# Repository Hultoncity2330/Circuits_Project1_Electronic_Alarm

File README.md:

# Projet Réveil Électronique

Projet de conception d’un **réveil électronique** réalisé sous **KiCad**.  
Le dépôt contient le schéma électronique, le PCB routé, les fichiers du projet KiCad ainsi que plusieurs vues du circuit final.

## Présentation du projet

L’objectif est de concevoir un réveil électronique compact capable d’afficher l’heure sur **4 digits 7 segments**, de gérer l’heure grâce à une horloge temps réel, et de proposer une interface utilisateur simple à l’aide de boutons poussoirs.

Le circuit est organisé autour d’un **Seeed Studio XIAO ESP32-S3**, utilisé comme microcontrôleur principal.

Le PCB comprend notamment :

- un **XIAO ESP32-S3** ;
- un **RTC RV-3028-C7** pour la gestion de l’heure ;
- un **IS31FL3730** pour le pilotage des afficheurs ;
- deux afficheurs doubles **DC56-11EWA**, soit 4 digits au total ;
- un buzzer pour l’alarme ;
- un transistor MOSFET **AO3400A** pour commander le buzzer ;
- quatre boutons poussoirs : `SET`, `ALARM`, `MINUS`, `PLUS` ;
- trois LED d’indication ;
- les résistances et condensateurs nécessaires au fonctionnement du montage.

## Fonctionnement général

Le **XIAO ESP32-S3** constitue le cœur du système.

Le **RV-3028-C7** fournit l’heure au microcontrôleur via le bus **I²C** (`SDA` / `SCL`).

Le **IS31FL3730** est également relié au bus I²C et pilote les deux afficheurs 7 segments. Les deux afficheurs doubles permettent d’obtenir un affichage sur quatre chiffres.

Les boutons permettent l’interaction avec le réveil :

- `SET` : réglage ;
- `ALARM` : gestion de l’alarme ;
- `PLUS` : incrémentation ;
- `MINUS` : décrémentation.

Le buzzer est commandé par le XIAO au travers du MOSFET **AO3400A**.

## Schéma électronique

Le schéma final du projet est disponible ci-dessous :

Le fichier source KiCad correspondant est :

`Projet_Réveil_électronique.kicad_sch`

## PCB

Le PCB a été placé et routé sous KiCad sur deux couches :

- **F.Cu** : couche cuivre supérieure ;
- **B.Cu** : couche cuivre inférieure.

Le routage utilise également :

- un plan de cuivre **+3.3 V** sur la face supérieure ;
- un plan de masse **GND** sur la face inférieure.

Vue du PCB final :

Le fichier source du PCB est :

`Projet_Réveil_électronique.kicad_pcb`

## Modèle 3D

### Front view

### Back view

### Perspective view

## Validation KiCad

Le projet a été vérifié avec les outils de contrôle de KiCad.

À la fin du routage :

- **ERC** du schéma : validé ;
- **DRC** du PCB : `0` erreur ;
- **Items non connectés** : `0` ;
- **Parité schématique / PCB** : `0` erreur.

Cela permet de vérifier la cohérence électrique et le routage du projet avant la fabrication.

> La validation ERC/DRC ne remplace pas un test physique du PCB assemblé.  
> Le fonctionnement réel doit être confirmé après soudure et mise sous tension.

## Structure du dépôt

```text
.
├── Projet_Réveil_électronique.kicad_pro
├── Projet_Réveil_électronique.kicad_sch
├── Projet_Réveil_électronique.kicad_pcb
├── Schematic_Réveil_électronique_VF.png
├── PCB_VF.png
├── PCB_3D_Model_Front.png
├── PCB_3D_Model_Back.png
├── PCB_3D_Model_Perspective.png
├── .gitignore
└── README.md
```

## Fichiers principaux

| Fichier | Description |
|---|---|
| `Projet_Réveil_électronique.kicad_pro` | Fichier principal du projet KiCad |
| `Projet_Réveil_électronique.kicad_sch` | Schéma électronique |
| `Projet_Réveil_électronique.kicad_pcb` | PCB routé |
| `Schematic_Réveil_électronique_VF.png` | Image du schéma final |
| `PCB_VF.png` | Vue du PCB final |
| `PCB_3D_Model_Front.png` | Vue 3D avant |
| `PCB_3D_Model_Back.png` | Vue 3D arrière |
| `PCB_3D_Model_Perspective.png` | Vue 3D en perspective |

## Auteur

Projet réalisé dans le cadre du cours `Circuits & Embedded Devices` du `21-23/09/2026`.

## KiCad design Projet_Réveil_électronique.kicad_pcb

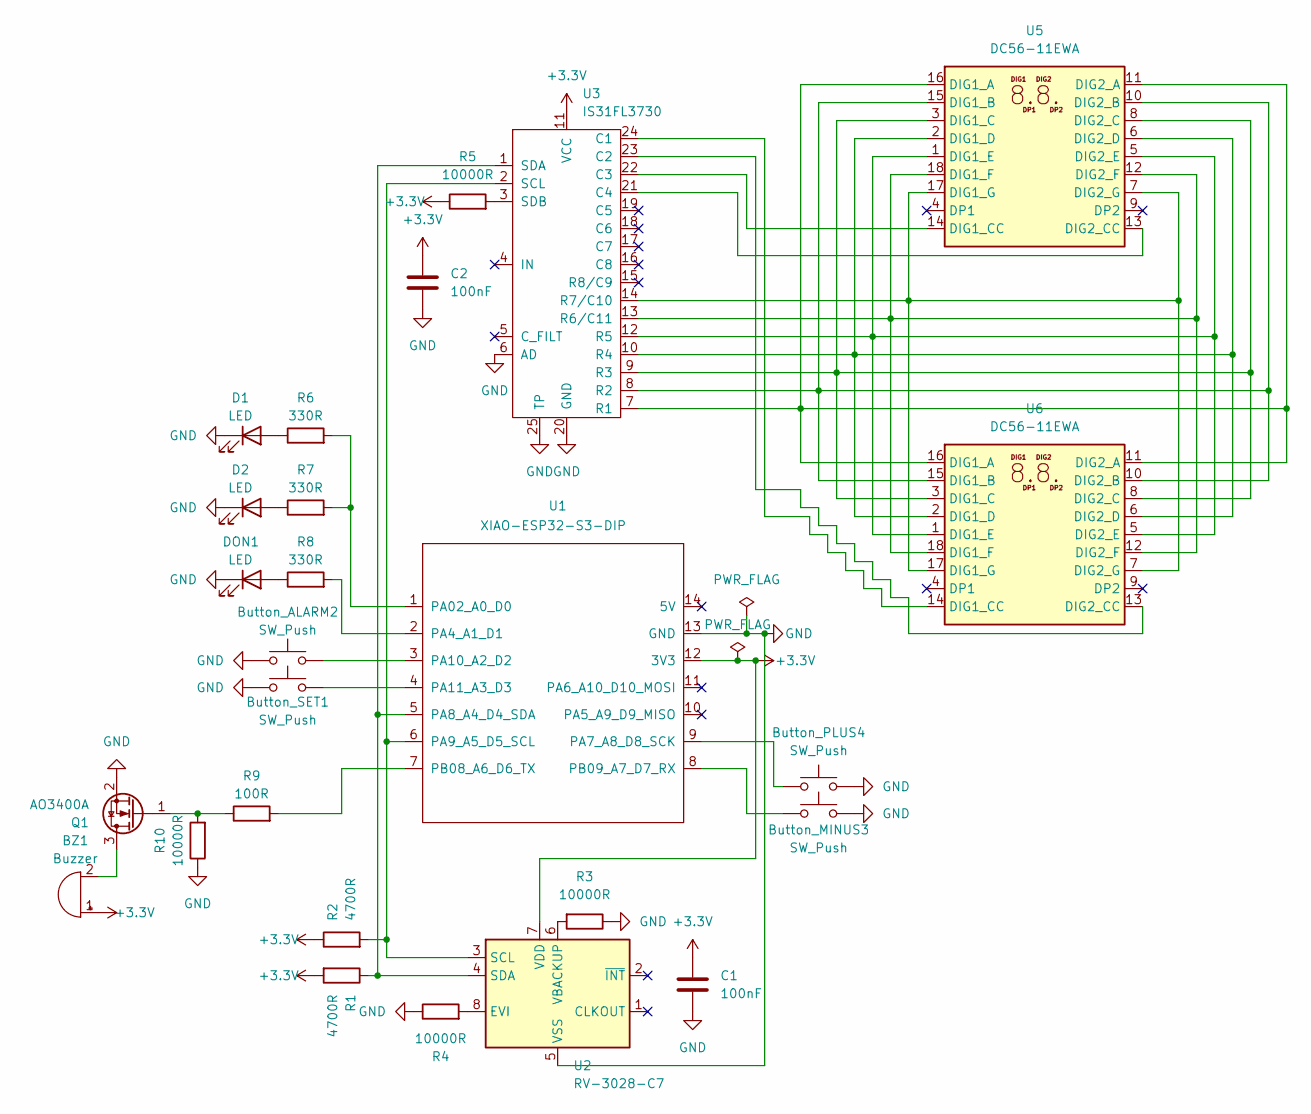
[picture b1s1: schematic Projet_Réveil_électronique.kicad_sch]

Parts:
BZ1: Buzzer; Buzzer_12x9.5RM7.6
Button_ALARM2: SW_Push; SW_PUSH_6mm
Button_MINUS3: SW_Push; SW_PUSH_6mm
Button_PLUS4: SW_Push; SW_PUSH_6mm
Button_SET1: SW_Push; SW_PUSH_6mm
C1, C2: 100nF; C_0805_2012Metric
D1, D2: LED; LED_0805_2012Metric
DON1: LED; LED_0805_2012Metric
Q1: AO3400A; SOT-23
R1, R2: 4700R; R_0805_2012Metric
R3, R4, R5, R10: 10000R; R_0805_2012Metric
R6, R7, R8: 330R; R_0805_2012Metric
R9: 100R; R_0805_2012Metric
U1: XIAO-ESP32-S3-DIP
U2: RV-3028-C7; MicroCrystal_C7_SON-8_1.5x3.2mm_P0.9mm
U3: IS31FL3730; QFN-24-1EP_4x4mm_P0.5mm_EP2.6x2.6mm
U5, U6: DC56-11EWA; DA56-11SURKWA

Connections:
+3.3V: BZ1.1 (+), C1.1, C2.1, R1.2, R2.1, R5.1, U1.12 (3V3), U2.7 (VDD), U3.11 (VCC)
GND: Button_ALARM2.1, Button_MINUS3.2, Button_PLUS4.2, Button_SET1.1, C1.2, C2.2, D1.1 (K), D2.1 (K), DON1.1 (K), Q1.2 (S), R3.1, R4.1, R10.1, U1.13 (GND), U2.5 (VSS), U3.6 (AD), U3.20 (GND), U3.25 (TP)
unnamed: BZ1.2 (-), Q1.3 (D)
unnamed: D1.2 (A), R6.1
unnamed: D2.2 (A), R7.1
unnamed: DON1.2 (A), R8.1
unnamed: Q1.1 (G), R9.1, R10.2
unnamed: R6.2, R7.2, U1.1 (PA02_A0_D0)
unnamed: R8.2, U1.2 (PA4_A1_D1)
unnamed: Button_PLUS4.1, U1.9 (PA7_A8_D8_SCK)
unnamed: R1.1, U1.5 (PA8_A4_D4_SDA), U2.4 (SDA), U3.1 (SDA)
unnamed: R2.2, U1.6 (PA9_A5_D5_SCL), U2.3 (SCL), U3.2 (SCL)
unnamed: Button_ALARM2.2, U1.3 (PA10_A2_D2)
unnamed: Button_SET1.2, U1.4 (PA11_A3_D3)
unnamed: R9.2, U1.7 (PB08_A6_D6_TX)
unnamed: Button_MINUS3.1, U1.8 (PB09_A7_D7_RX)
unnamed: R4.2, U2.8 (EVI)
unnamed: R3.2, U2.6 (VBACKUP)
unnamed: U3.24 (C1), U6.14 (DIG1_CC)
unnamed: U3.23 (C2), U6.13 (DIG2_CC)
unnamed: U3.22 (C3), U5.14 (DIG1_CC)
unnamed: U3.21 (C4), U5.13 (DIG2_CC)
unnamed: U3.7 (R1), U5.11 (DIG2_A), U5.16 (DIG1_A), U6.11 (DIG2_A), U6.16 (DIG1_A)
unnamed: U3.8 (R2), U5.10 (DIG2_B), U5.15 (DIG1_B), U6.10 (DIG2_B), U6.15 (DIG1_B)
unnamed: U3.9 (R3), U5.3 (DIG1_C), U5.8 (DIG2_C), U6.3 (DIG1_C), U6.8 (DIG2_C)
unnamed: U3.10 (R4), U5.2 (DIG1_D), U5.6 (DIG2_D), U6.2 (DIG1_D), U6.6 (DIG2_D)
unnamed: U3.12 (R5), U5.1 (DIG1_E), U5.5 (DIG2_E), U6.1 (DIG1_E), U6.5 (DIG2_E)
unnamed: U3.13 (R6/C11), U5.12 (DIG2_F), U5.18 (DIG1_F), U6.12 (DIG2_F), U6.18 (DIG1_F)
unnamed: U3.14 (R7/C10), U5.7 (DIG2_G), U5.17 (DIG1_G), U6.7 (DIG2_G), U6.17 (DIG1_G)
unnamed: R5.2, U3.3 (SDB)

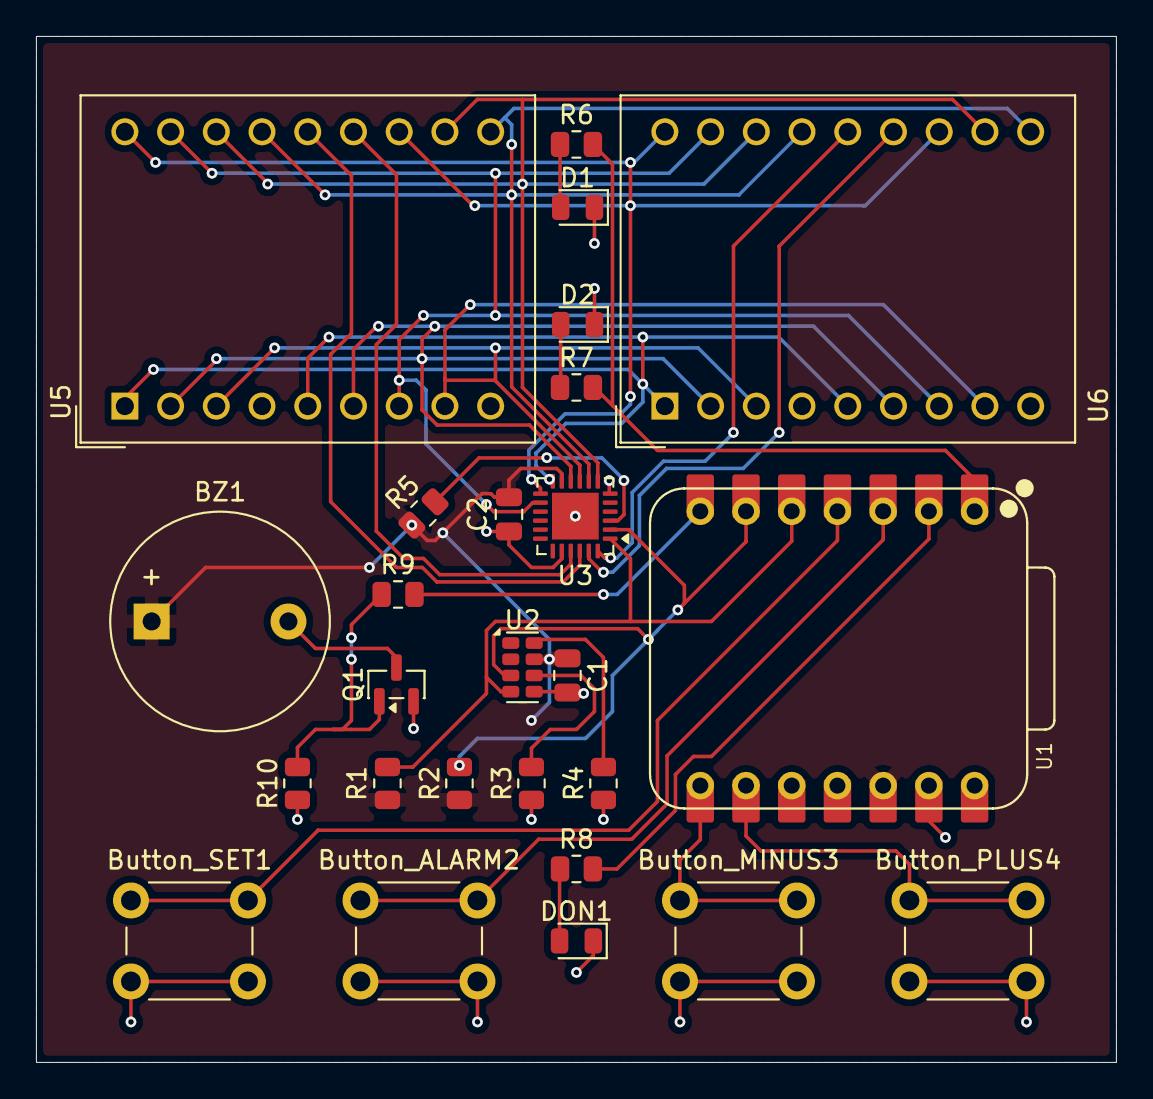
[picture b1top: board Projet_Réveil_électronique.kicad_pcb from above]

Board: 2 copper layers, 60.0 x 57.0 mm, 26 parts (0 on the bottom side), 30 nets.
